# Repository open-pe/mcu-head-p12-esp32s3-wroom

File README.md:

This is a break-out for an ESP32-WROOM or ESP32S3-WROOM module.
These modules can be hard to desolder, if the chip gets damaged during development.
You can mount this break-out board using 2.54mm pitch standard pin connectors (SMD) on a mainboard for easier
replacement.

The footprint of the landing connector on the mainboard fits inside the WROOM-Footprint so it does not need extra space
on the mainboard (only wiring due to the extra pads can be a bit more complicated).
During assembly you can either populate the WROOM module directly on the mainboard or use this break-out board.

|                                           |
|--------------------------------------------------------------------------------------------------|
| blue: WROOM footprint pads <br/>red: 2.54mm SMD pin header pads to receive this break-out board. |

It also works on solderless breadboards.

## Features
* ESP-PROG header
* USB pin header
* USB-C socket
* BOOT button (GPIO0) to enter download mode manually
* 3.3V LDO regulator

# Notes

## LDOs 5V to 3.3V

* NCP167BMX330TBG
* TLV70233_SOT23-5

## 3.3-5V boost

if we put the ESP32S3 in USB host mode and supply 5V on the USB-C port we can connect arbitrary usb devices.
[digikey boost](https://www.digikey.de/short/q9n4rhhj)

* TPS631000DRLR
* TPS61094 (bi-directional) kicad symbol: https://github.com/JY68-Werable-EEG-Sensor/Wearable-EEG-Sensor
    * this might replace the 5V to 3.3V LDO.

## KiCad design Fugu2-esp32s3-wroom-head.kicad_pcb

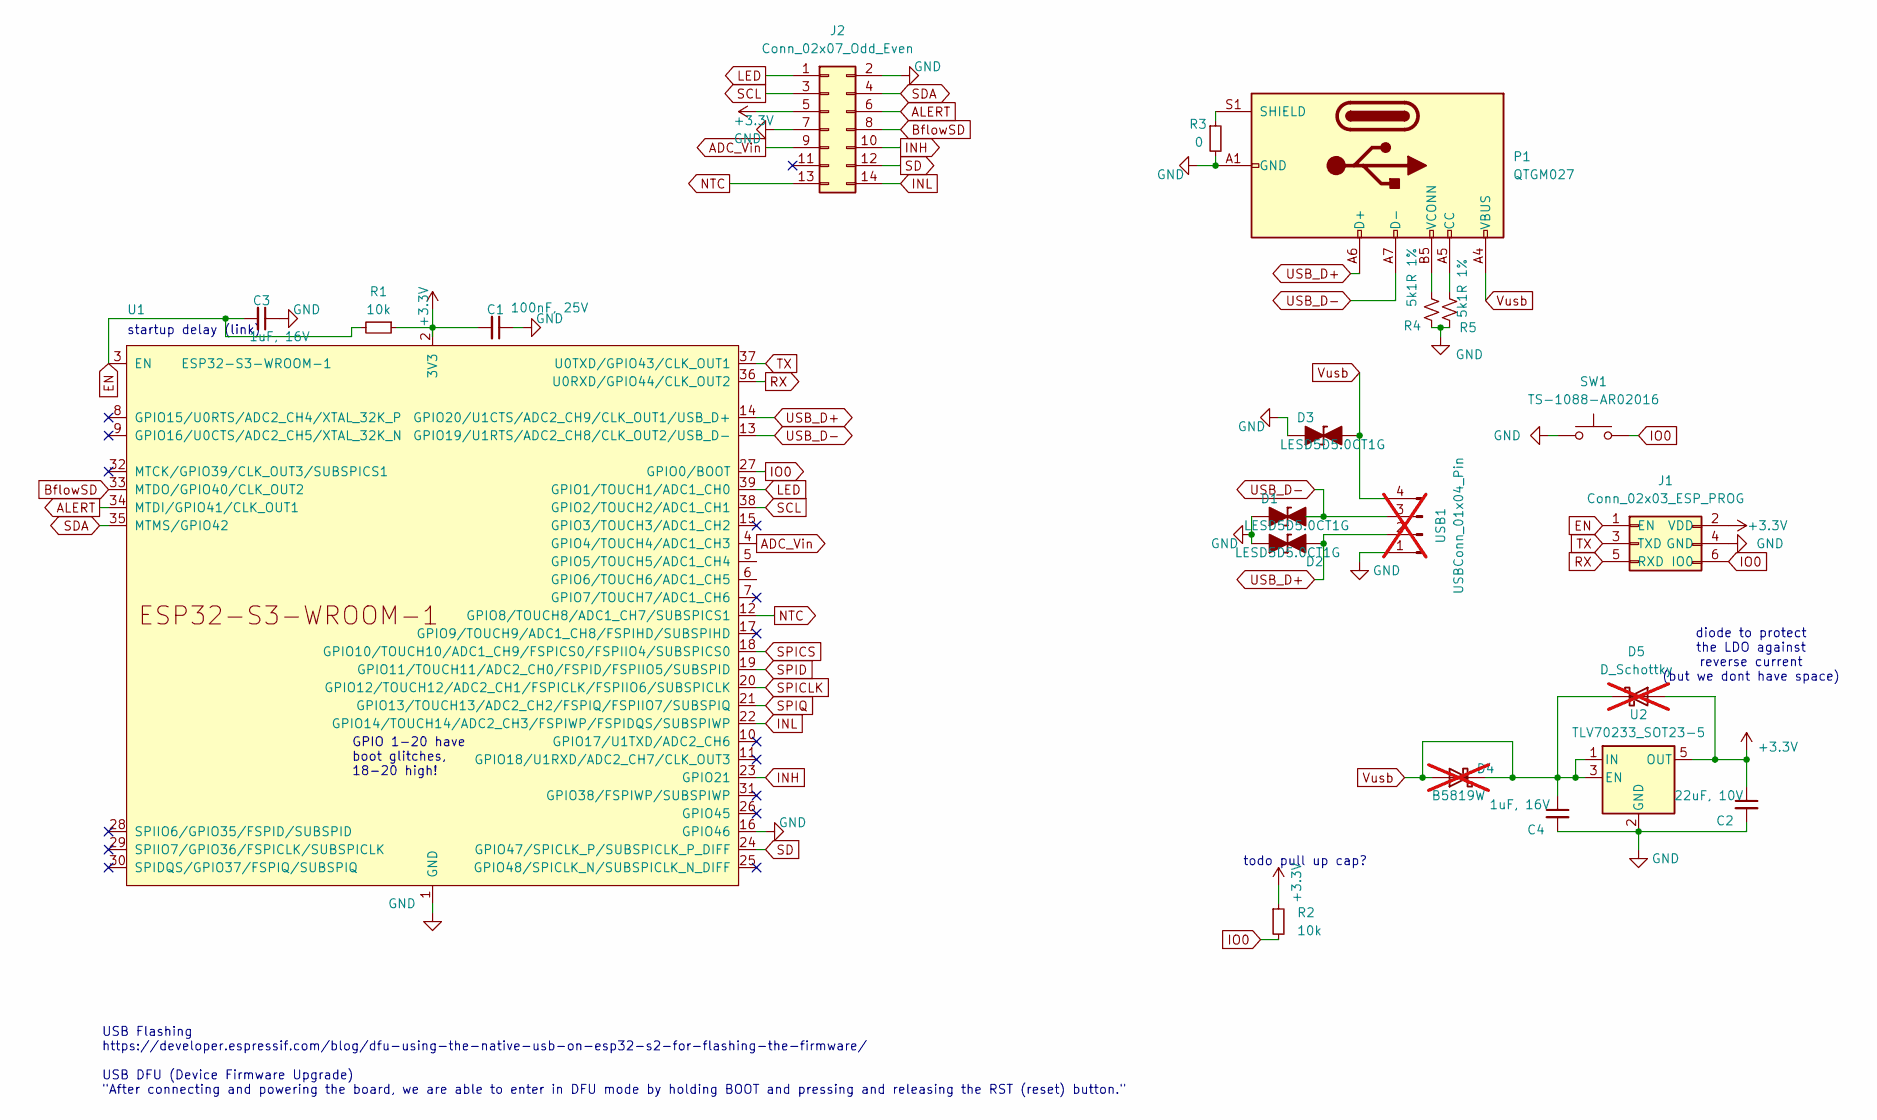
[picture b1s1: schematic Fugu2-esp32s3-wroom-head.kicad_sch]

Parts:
C1: 100nF, 25V; C_0805_2012Metric; MPN 100nF
C2: 22uF, 10V; C_0603_1608Metric_Pad1.08x0.95mm_HandSolder; MPN 1uF, 16V; Digikey CL10A226MP8NUNE
C3, C4: 1uF, 16V; C_0805_2012Metric; MPN 1uF, 16V
D1, D2, D3: LESD5D5.0CT1G; D_SOD-523; MPN LESD5D5.0CT1G; LCSC C383211
D4: B5819W; D_SOD-123; MPN DNP; LCSC C8598; not fitted
D5: D_Schottky; D_SOD-123; not fitted
J1: Conn_02x03_ESP_PROG; PinHeader_2x03_P2.54mm_Vertical; MPN DNP
J2: Conn_02x07_Odd_Even; PinHeader_2x07_P2.54mm_Vertical_SMD_Pin1Left_1; MPN Samtec SSM-107-L-SV; LCSC C7017504, Samtec SSM-107-L-SV
P1: QTGM027; USB_C_Receptacle_GCT_USB4110; MPN SHOU HAN TYPE-C 16P QTGM027; LCSC C2681552
R1, R2: 10k; R_0805_2012Metric; MPN 10k
R3: 0; R_0402_1005Metric; MPN 0; LCSC C17168
R4, R5: 5k1R 1%; R_0402_1005Metric; MPN 5k1R 1%; LCSC C25905
SW1: TS-1088-AR02016; SW_Push_SPST_NO_Alps_SKRK; MPN XUNPU TS-1088-AR02016; LCSC C720477
U1: ESP32-S3-WROOM-1; ESP32-S3-WROOM-1-noPIN15; MPN ESP32-S3-WROOM-1U-N4
U2: TLV70233_SOT23-5; SOT-23-5; MPN TLV70233DBVR; LCSC C26833
USB1: USBConn_01x04_Pin; PinHeader_1x04_P2.54mm_Vertical; MPN DNP; not fitted

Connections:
+3.3V: C1.2, C2.1, D5.2 (A), J1.2 (VDD), J2.5, R1.1, R2.1, U1.2 (3V3), U2.5 (OUT)
ADC_Vin: J2.9, U1.4 (GPIO4/TOUCH4/ADC1_CH3)
ALERT: J2.6, U1.34 (MTDI/GPIO41/CLK_OUT1)
BflowSD: J2.8, U1.33 (MTDO/GPIO40/CLK_OUT2)
EN: C3.2, J1.1 (EN), R1.2, U1.3 (EN)
GND: C1.1, C2.2, C3.1, C4.2, D1.2 (A), D2.2 (A), D3.2 (A), J1.4 (GND), J2.2, J2.7, P1.A1 (GND), P1.A12 (GND), P1.B1 (GND), P1.B12 (GND), R3.2, R4.2, R5.2, SW1.1, U1.1 (GND), U1.16 (GPIO46), U1.40 (GND), U1.41 (GND), U2.2 (GND), USB1.1
INH: J2.10, U1.23 (GPIO21)
INL: J2.14, U1.22 (GPIO14/TOUCH14/ADC2_CH3/FSPIWP/FSPIDQS/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)
IO0: J1.6 (IO0), R2.2, SW1.2, U1.27 (GPIO0/BOOT)
LED: J2.1, U1.39 (GPIO1/TOUCH1/ADC1_CH0)
NTC: J2.13, U1.12 (GPIO8/TOUCH8/ADC1_CH7/SUBSPICS1)
unnamed: P1.A5 (CC), R5.1
unnamed: P1.S1 (SHIELD), R3.1
unnamed: P1.B5 (VCONN), R4.1
RX: J1.5 (RXD), U1.36 (U0RXD/GPIO44/CLK_OUT2)
SCL: J2.3, U1.38 (GPIO2/TOUCH2/ADC1_CH1)
SD: J2.12, U1.24 (GPIO47/SPICLK_P/SUBSPICLK_P_DIFF)
SDA: J2.4, U1.35 (MTMS/GPIO42)
SPICLK: U1.20 (GPIO12/TOUCH12/ADC2_CH1/FSPICLK/FSPIIO6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)
SPICS: U1.18 (GPIO10/TOUCH10/ADC1_CH9/FSPICS0/FSPIIO4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)
SPID: U1.19 (GPIO11/TOUCH11/ADC2_CH0/FSPID/FSPIIO5/S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)
SPIQ: U1.21 (GPIO13/TOUCH13/ADC2_CH2/FSPIQ/FSPIIO7/S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)
TX: J1.3 (TXD), U1.37 (U0TXD/GPIO43/CLK_OUT1)
USB_D+: D2.1 (K), P1.A6 (D+), U1.14 (GPIO20/U1CTS/ADC2_CH9/CLK_OUT1/USB_D+), USB1.2
USB_D-: D1.1 (K), P1.A7 (D-), U1.13 (GPIO19/U1RTS/ADC2_CH8/CLK_OUT2/USB_D-), USB1.3
Vusb: C4.1, D3.1 (K), D4.1 (K), D4.2 (A), D5.1 (K), P1.A4 (VBUS), P1.A9 (VBUS), P1.B4 (VBUS), P1.B9 (VBUS), U2.1 (IN), U2.3 (EN), USB1.4

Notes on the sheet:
startup delay (link)
diode to protect the LDO against reverse current (but we dont have space)
GPIO 1-20 have boot glitches, 18-20 high!
todo pull up cap?
USB Flashing https://developer.espressif.com/blog/dfu-using-the-native-usb-on-esp32-s2-for-flashing-the-firmware/ USB DFU (Device Firmware Upgrade) "After connecting and powering the board, we are able to enter in DFU mode by holding BOOT and pressing and releasing the RST (reset) button."

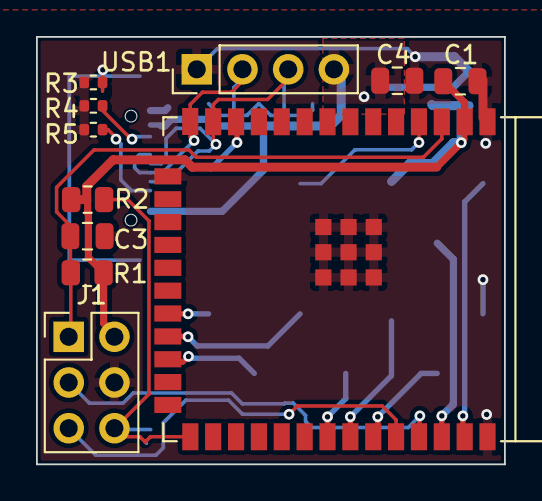
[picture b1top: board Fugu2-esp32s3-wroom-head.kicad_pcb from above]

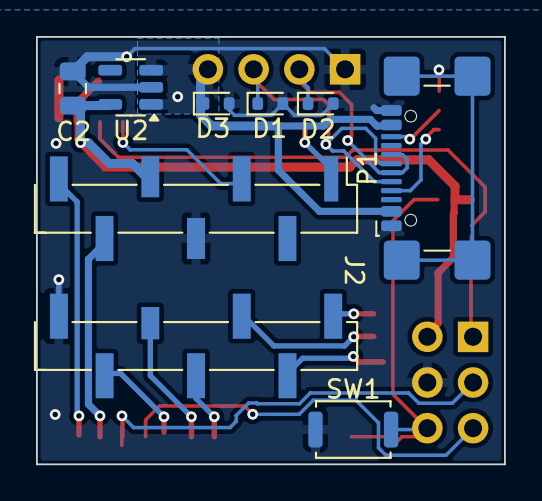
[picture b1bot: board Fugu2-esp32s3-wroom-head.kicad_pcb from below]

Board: 2 copper layers, 26.0 x 23.7 mm, 19 parts (8 on the bottom side), 22 nets.

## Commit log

2024-11-03 Intial commit
2024-11-07 add 3d renderings
2024-11-07 add schematic
2024-12-05 fix button
2025-09-25 bump kicad version
2025-11-28 readme
2025-11-28 add footprint image
